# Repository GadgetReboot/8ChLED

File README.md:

# 8ChLED
8 Addressable LEDs show logic input high/low states for easy probing
<br><br><BR><BR>

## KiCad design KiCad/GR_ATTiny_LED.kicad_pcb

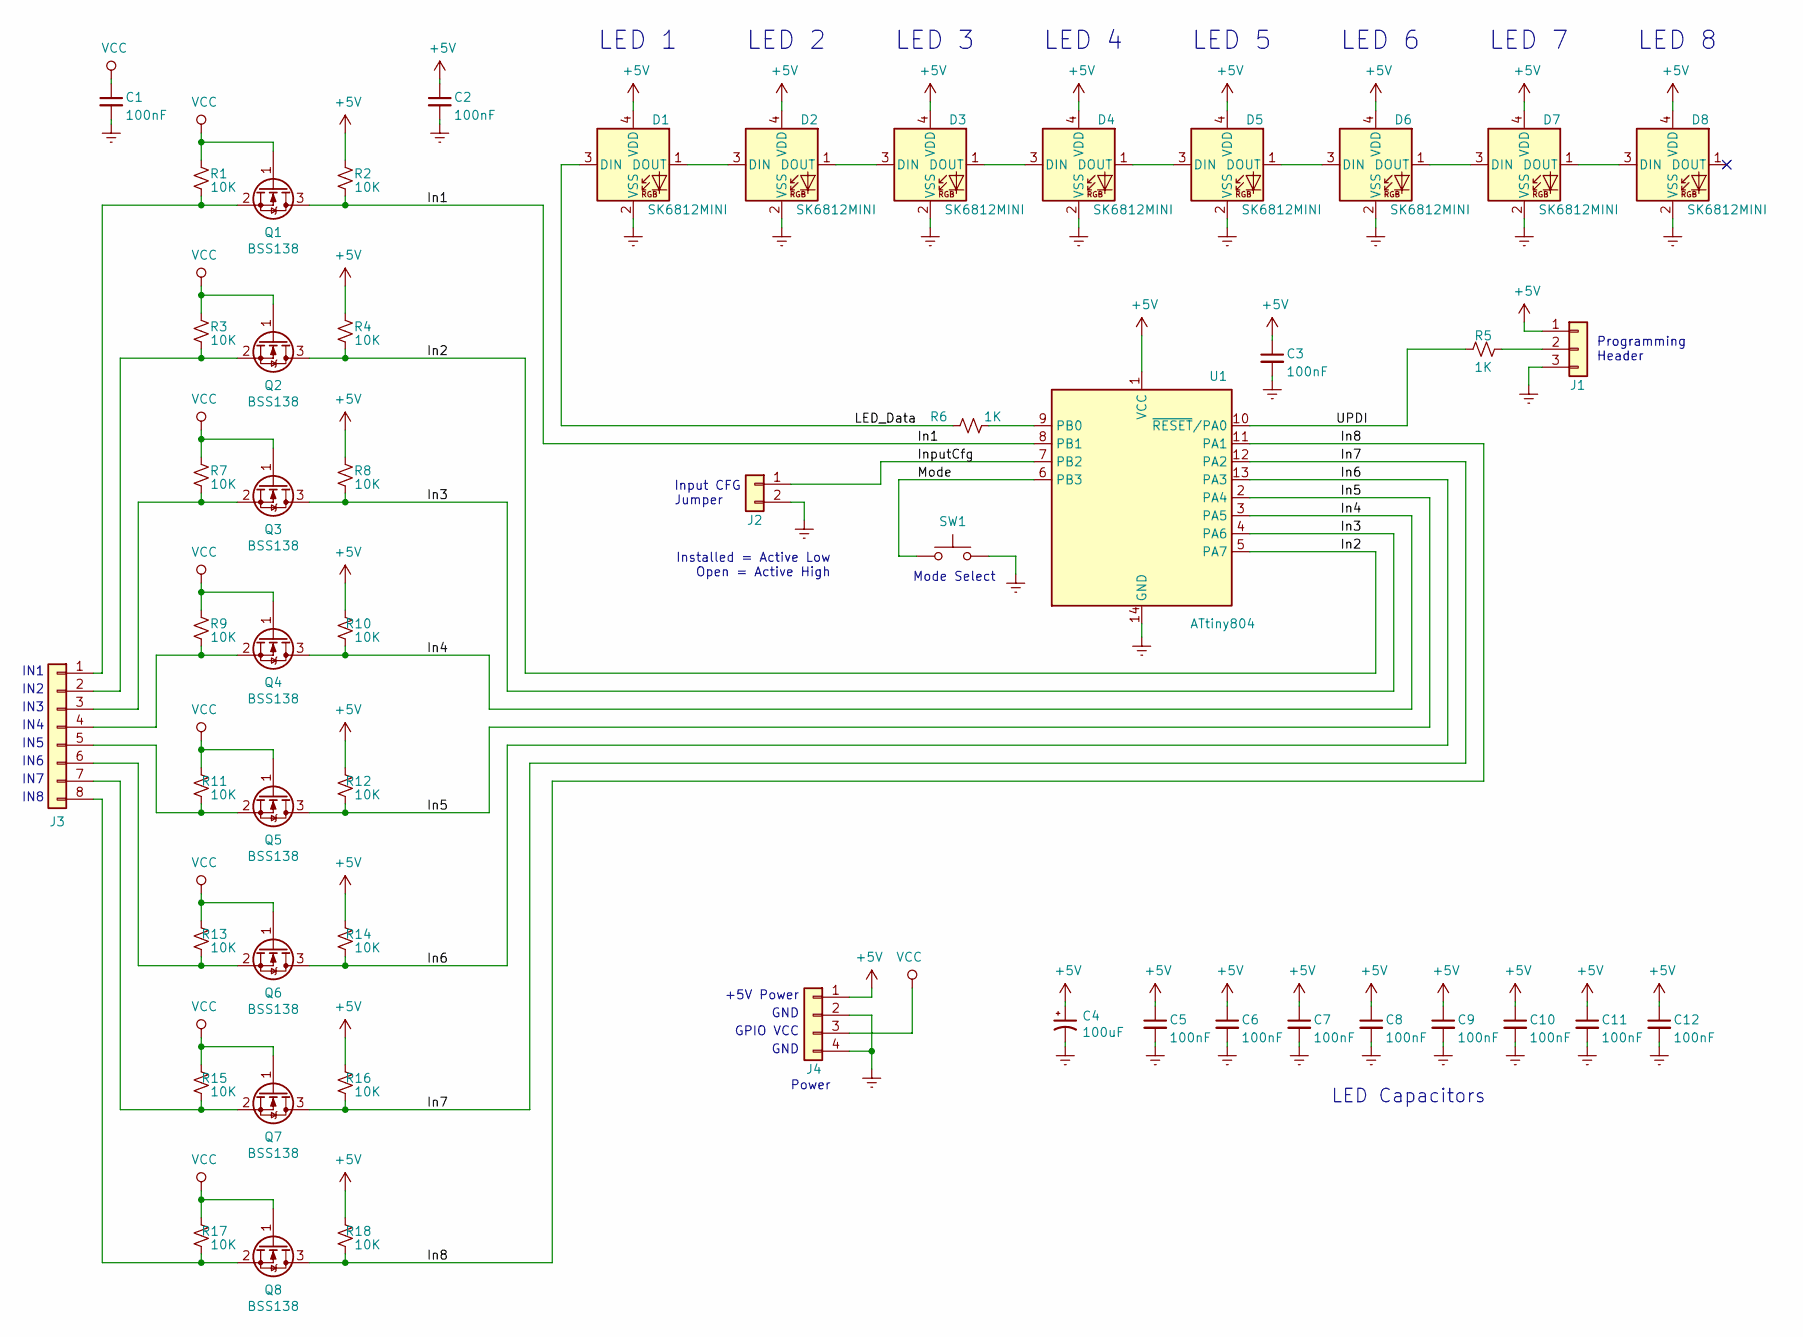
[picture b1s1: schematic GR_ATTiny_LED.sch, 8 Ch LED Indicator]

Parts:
C1, C2, C3, C5, C6, C7, C8, C9, C10, C11, C12: 100nF; C_0805_2012Metric_Pad1.15x1.40mm_HandSolder
C4: 100uF; C_Elec_6.3x5.8
D1, D2, D3, D4, D5, D6, D7, D8: SK6812MINI; LED_SK6812MINI_4_3.5x3.5mm_P1.75mm
J1: Conn_01x03; PinHeader_1x03_P2.54mm_Vertical
J2: Conn_01x02; PinHeader_1x02_P2.54mm_Vertical
J3: Conn_01x08; PinHeader_1x08_P2.54mm_Vertical
J4: Conn_01x04; PinHeader_1x04_P2.54mm_Vertical
Q1, Q2, Q3, Q4, Q5, Q6, Q7, Q8: BSS138; SOT-23
R1, R2, R3, R4, R7, R8, R9, R10, R11, R12, R13, R14, R15, R16, R17, R18: 10K; R_0805_2012Metric_Pad1.15x1.40mm_HandSolder
R5, R6: 1K; R_0805_2012Metric_Pad1.15x1.40mm_HandSolder
SW1: SW_Push; SW_SPST_60x35
U1: ATtiny804; SOIC-14_3.9x8.7mm_P1.27mm

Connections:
+5V: C2.1, C3.1, C4.1, C5.1, C6.1, C7.1, C8.1, C9.1, C10.1, C11.1, C12.1, D1.4 (VDD), D2.4 (VDD), D3.4 (VDD), D4.4 (VDD), D5.4 (VDD), D6.4 (VDD), D7.4 (VDD), D8.4 (VDD), J1.1, J4.1, R2.1, R4.1, R8.1, R10.1, R12.1, R14.1, R16.1, R18.1, U1.1 (VCC)
/In1: Q1.3 (D), R2.2, U1.8 (PB1)
/In2: Q2.3 (D), R4.2, U1.5 (PA7)
/In3: Q3.3 (D), R8.2, U1.4 (PA6)
/In4: Q4.3 (D), R10.2, U1.3 (PA5)
/In5: Q5.3 (D), R12.2, U1.2 (PA4)
/In6: Q6.3 (D), R14.2, U1.13 (PA3)
/In7: Q7.3 (D), R16.2, U1.12 (PA2)
/In8: Q8.3 (D), R18.2, U1.11 (PA1)
/InputCfg: J2.1, U1.7 (PB2)
/LED_Data: D1.3 (DIN), R6.2
/Mode: SW1.1, U1.6 (PB3)
/UPDI: R5.2, U1.10 (~RESET~/PA0)
GNDREF: C1.2, C2.2, C3.2, C4.2, C5.2, C6.2, C7.2, C8.2, C9.2, C10.2, C11.2, C12.2, D1.2 (VSS), D2.2 (VSS), D3.2 (VSS), D4.2 (VSS), D5.2 (VSS), D6.2 (VSS), D7.2 (VSS), D8.2 (VSS), J1.3, J2.2, J4.2, J4.4, SW1.2, U1.14 (GND)
unnamed: D1.1 (DOUT), D2.3 (DIN)
unnamed: D2.1 (DOUT), D3.3 (DIN)
unnamed: D3.1 (DOUT), D4.3 (DIN)
unnamed: D4.1 (DOUT), D5.3 (DIN)
unnamed: D5.1 (DOUT), D6.3 (DIN)
unnamed: D6.1 (DOUT), D7.3 (DIN)
unnamed: D7.1 (DOUT), D8.3 (DIN)
unnamed: J1.2, R5.1
unnamed: J3.1, Q1.2 (S), R1.2
unnamed: J3.2, Q2.2 (S), R3.2
unnamed: J3.3, Q3.2 (S), R7.2
unnamed: J3.4, Q4.2 (S), R9.2
unnamed: J3.5, Q5.2 (S), R11.2
unnamed: J3.6, Q6.2 (S), R13.2
unnamed: J3.7, Q7.2 (S), R15.2
unnamed: J3.8, Q8.2 (S), R17.2
unnamed: R6.1, U1.9 (PB0)
VCC: C1.1, J4.3, Q1.1 (G), Q2.1 (G), Q3.1 (G), Q4.1 (G), Q5.1 (G), Q6.1 (G), Q7.1 (G), Q8.1 (G), R1.1, R3.1, R7.1, R9.1, R11.1, R13.1, R15.1, R17.1

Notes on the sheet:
Programming Header
LED Capacitors
LED 1
LED 2
LED 3
LED 4
LED 5
LED 6
LED 7
LED 8
IN1
IN2
IN3
IN4
IN5
IN6
IN7
IN8
Input CFG Jumper
Installed = Active Low Open = Active High
Mode Select
Power
GND
GPIO VCC
+5V Power

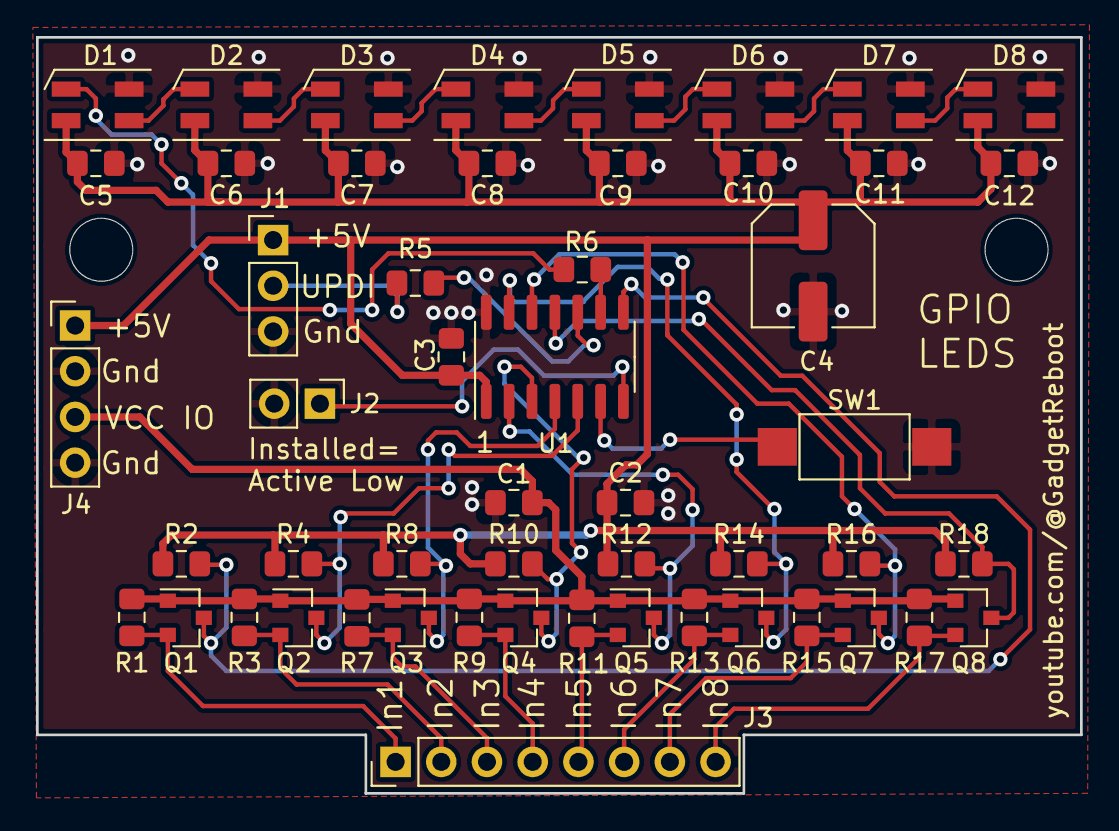
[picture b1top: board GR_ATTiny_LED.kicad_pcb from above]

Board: 2 copper layers, 58.0 x 42.0 mm, 52 parts (0 on the bottom side), 32 nets.

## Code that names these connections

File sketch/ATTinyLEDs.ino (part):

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#include <tinyNeoPixel_Static.h>  // part of the megatinecore board file
#include <Bounce2.h>              // debounce https://github.com/thomasfredericks/Bounce2

#define dataPin   7               // ATTiny804 PB0 is Arduino pin 7 (see megaTinyCore on Github)
#define cfgPin    5               // ATTiny804 PB2 is Arduino pin 5
#define modePin   4               // ATTiny804 PB3 is Arduino pin 4
#define input1    6               // ATTiny804 PB1 is Arduino pin 6
#define input2    3               // ATTiny804 PA7 is Arduino pin 3
#define input3    2               // ATTiny804 PA6 is Arduino pin 2
#define input4    1               // ATTiny804 PA5 is Arduino pin 1
#define input5    0               // ATTiny804 PA4 is Arduino pin 0
#define input6    10              // ATTiny804 PA3 is Arduino pin 10
#define input7    9               // ATTiny804 PA2 is Arduino pin 9
#define input8    8               // ATTiny804 PA1 is Arduino pin 8

const byte NUMPIXELS = 8;         // pcb has 8 SK6812 LEDs
byte pixels[NUMPIXELS * 3];
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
